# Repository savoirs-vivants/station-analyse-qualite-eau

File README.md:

# Station d'Analyse de la Qualité de l'Eau 💧

Station autonome pour la surveillance de la qualité de l'eau. Ce dépôt contient l'intégralité de la conception matérielle (schémas et routage PCB) ainsi que le firmware d'acquisition.

## 🎯 Objectif du projet

Ce système a pour but de collecter, traiter, transmettre et enregistrer des données environnementales issues de différentes sondes. Il est conçu pour être autonome en énergie et low-cost.

**Paramètres mesurés :**
*  Température de l'eau
*  Température et Humidité de l'air
*  Conductivité / TDS
*  Turbidité
*  Débit/Hauteur d'eau

## 📁 Architecture du projet

Ce dépôt est organisé en deux parties distinctes :

* 🛠️ **`/hardware`** : Fichiers de conception de la carte électronique réalisés sous KiCad (Schémas, PCB, nomenclatures).
* 💻 **`/firmware`** : Code source en C gérant l'acquisition , le traitement des signaux capteurs et la logique système.

*Pour plus de détails techniques, veuillez consulter les fichiers `README.md` présents dans chacun de ces répertoires.*

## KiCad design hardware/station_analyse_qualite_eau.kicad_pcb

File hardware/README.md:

# 🛠️ Conception Matérielle (Hardware)

Ce dossier contient l'intégralité du projet de conception de la carte mère de la **Station d'Analyse de la Qualité de l'Eau**. La carte est architecturée autour d'un microcontrôleur ultra-basse consommation **STM32U083RC**.

## 📌 Caractéristiques Techniques

* **Microcontrôleur :** STM32U083RC (ARM Cortex-M0+, optimisation Low-Power).
* **Mémoire non volatile :** FeRAM (Ferroelectric RAM) via bus SPI pour le datalogging.
* **Connectivité Radio :**
    * **LoRaWAN :** Module radio intégré pour la transmission vers réseau ChirpStack.
    * **Bluetooth Low Energy (BLE) :** Pour la récupération locale des données en cas de problème avec le LoRa.

## 📂 Architecture du dossier KiCad

* `*.kicad_sch` : Schémas électriques hiérarchiques.
* `*.kicad_pcb` : Routage de la carte.
* `/production` : Fichiers de fabrication générés pour JLCPCB.
* `/3D_Models` : Fichiers STEP pour le rendu 3D.

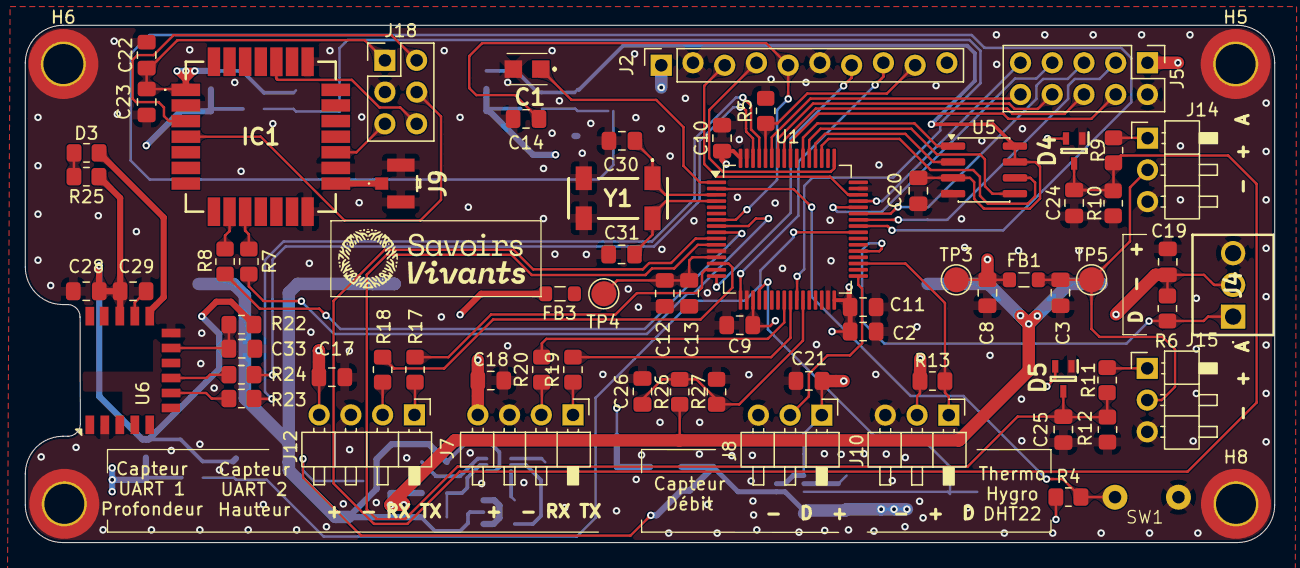
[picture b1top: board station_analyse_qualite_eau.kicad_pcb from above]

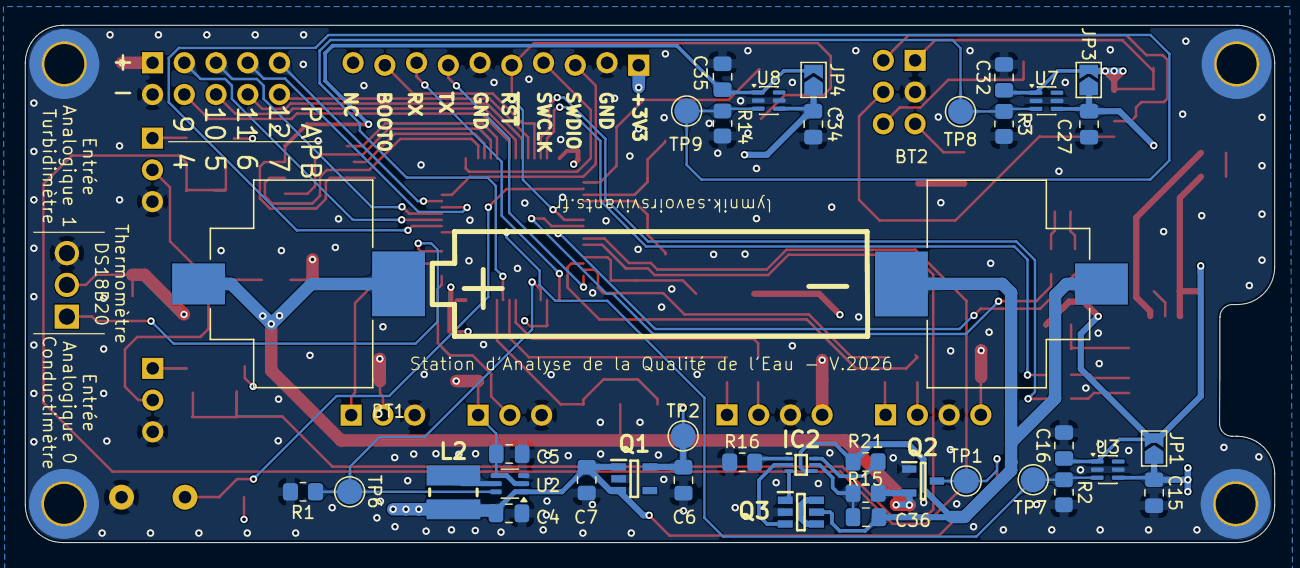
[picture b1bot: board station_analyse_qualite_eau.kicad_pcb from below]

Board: 4 copper layers, 100.0 x 41.4 mm, 112 parts (38 on the bottom side), 76 nets.

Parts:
BT1, BT2: 254; BAT_254
C1: CPH3225A
C2, C3, C4, C8, C22, C28: 10u; C_0805_2012Metric_Pad1.18x1.45mm_HandSolder
C5, C6: 2.2u; C_0805_2012Metric_Pad1.18x1.45mm_HandSolder
C7, C12, C15, C17, C18, C19, C21, C24, C25, C27, C34: 1u; C_0805_2012Metric_Pad1.18x1.45mm_HandSolder
C9, C10, C11, C13, C14, C16, C20, C23, C26, C29, C32, C33, C35, C36: 100n; C_0805_2012Metric_Pad1.18x1.45mm_HandSolder
C30, C31: 6.8p; C_0805_2012Metric_Pad1.18x1.45mm_HandSolder
D3: LED; R_0805_2012Metric_Pad1.20x1.40mm_HandSolder
D4, D5: BAV199W; SOT65P210X110-3N
FB1, FB3: BLM21AG601SH1D; L_0805_2012Metric_Pad1.05x1.20mm_HandSolder
H5, H6, H7, H8: MountingHole_Pad; MountingHole_3.2mm_M3_DIN965_Pad_TopBottom
IC1: 317990687
IC2: S-82B1AAB-I6T1U; SOTFL50P180X50-6N
J2: SWD+DEBUG UART; StaggeredHeader_1x10_P2.54mm_Vertical
J4: Terminal_DS18B20; TBC05031GG
J5: Conn_02x05_Odd_Even; PinHeader_2x05_P2.54mm_Vertical
J7: Conn_Capteur_UART_2; Custom_PinHeader_1x04_P2.54mm_Horizontal
J8: Terminal_Water_Flow_Sensor; Custom_PinHeader_1x03_P2.54mm_Horizontal
J9: U.FL; UFLRSMT10
J10: Conn_DHT22; Custom_PinHeader_1x03_P2.54mm_Horizontal
J12: Conn_Capteur_UART_1; Custom_PinHeader_1x04_P2.54mm_Horizontal
J14, J15: Conn_AN; Custom_PinHeader_1x03_P2.54mm_Horizontal
J18: Conn_02x03_Odd_Even; PinHeader_2x03_P2.54mm_Vertical
JP1: Bypass LS BLE; SolderJumper-2_P1.3mm_Open_TrianglePad1.0x1.5mm
JP3: Bypass LS LoRa; SolderJumper-2_P1.3mm_Open_TrianglePad1.0x1.5mm
JP4: Bypass LS FRAM; SolderJumper-2_P1.3mm_Open_TrianglePad1.0x1.5mm
L2: 4,7u; 744031004
Q1: TPS7A0233PDBVR; SOT95P280X145-5N
Q2: DMG2305UX-7; SOT96P240X115-3N
Q3: FDC6561AN; SOT95P280X110-6N
R1, R2, R3, R14: 100k; R_0805_2012Metric_Pad1.20x1.40mm_HandSolder
R4, R5, R9, R10, R11, R12, R22: 10k; R_0805_2012Metric_Pad1.20x1.40mm_HandSolder
R6, R13: 4.7k; R_0805_2012Metric_Pad1.20x1.40mm_HandSolder
R7, R8, R17, R18, R19, R20, R23, R24: 22R; R_0805_2012Metric_Pad1.20x1.40mm_HandSolder
R15: 330; R_0805_2012Metric_Pad1.20x1.40mm_HandSolder
R16, R21: 1k; R_0805_2012Metric_Pad1.20x1.40mm_HandSolder
R25: 330R; R_0805_2012Metric_Pad1.20x1.40mm_HandSolder
R26, R27: 1M; R_0805_2012Metric_Pad1.20x1.40mm_HandSolder
SW1: SW_Push; P5.08mm
TP1: TP_BATT; TestPoint_Pad_D2.0mm
TP2: TP_3V3; TestPoint_Pad_D2.0mm
TP3: TP_5V; TestPoint_Pad_D2.0mm
TP4: TP_3.3VA; TestPoint_Pad_D2.0mm
TP5: TP_5VA; TestPoint_Pad_D2.0mm
TP6: TP_EN_BOOST; TestPoint_Pad_D2.0mm
TP7: TP_EN_LS_BLE; TestPoint_Pad_D2.0mm
TP8: TP_EN_LS_LORA; TestPoint_Pad_D2.0mm
TP9: TP_EN_LS_FRAM; TestPoint_Pad_D2.0mm
U1: STM32U083RCTx; LQFP-64_10x10mm_P0.5mm
U2: TPS61222DCK; Texas_R-PDSO-G6
U3, U7, U8: SiP32431DR3; SOT-363_SC-70-6
U5: MB85RS2MTAPNF; SOIC-8_3.9x4.9mm_P1.27mm
U6: RN4871; Microchip_RN4871
Y1: G43270018

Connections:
1-Wire: J4.1, R6.2, U1.37 (PC6)
+3.3VA: C12.1, C13.1, FB3.2, TP4.1 (1_1), U1.13 (VDDA)
+3V3: C2.1, C6.2, C9.1, C10.1, C11.1, C15.1, C27.1, C34.1, D4.2 (K), D5.2 (K), FB3.1, J2.1, J5.1, JP1.1 (A), JP3.1 (A), JP4.1 (A), Q1.5 (OUT), R4.1, TP2.1 (1_1), U1.19 (VDD), U1.32 (VDD), U1.64 (VDD), U3.4 (IN), U7.4 (IN), U8.4 (IN)
+3V3_BLE: C16.1, C28.1, C29.1, D3.2 (A), JP1.2 (B), R22.2, U3.1 (OUT), U6.14 (VBAT)
+3V3_FRAM: C20.1, C35.1, JP4.2 (B), U5.3 (~WP), U5.7 (~HOLD), U5.8 (VDD), U8.1 (OUT)
+3V3_LoRa: C22.1, C23.1, C32.1, IC1.1 (VCC), J18.1, JP3.2 (B), U7.1 (OUT)
+5V: C5.2, C8.2, C17.1, C18.1, C19.1, C21.1, FB1.1, J4.2, J7.4, J8.1, J10.2, J12.4, R6.1, R13.1, TP3.1 (1_1), U2.2 (FB), U2.4 (VOUT)
+5VA: C3.2, FB1.2, J14.2, J15.2, TP5.1 (1_1)
+BATT: BT1.P1, BT1.P2, Q2.2 (S), R15.2, R26.1
-BATT: BT2.P1, BT2.P2, C36.2, IC2.4 (VSS), Q3.5 (S1), R21.1
/Radio Frequency/BOOT_LoRa: IC1.24 (PB13), J18.6
/Radio Frequency/RST_LoRa: IC1.17 (RST), J18.5
/Radio Frequency/SWCLK_LoRa: IC1.4 (PA14), J18.4
/Radio Frequency/SWDIO_LoRa: IC1.3 (PA13), J18.2
AI0: C25.1, D5.3 (C), R11.2, R12.1, U1.11 (PC3)
AI1: C24.1, D4.3 (C), R9.2, R10.1, U1.10 (PC2)
AN_Battery: C26.1, R26.2, R27.1, U1.27 (PB1)
BOOT0: J2.9, R5.1, U1.60 (PF3)
DHT22: J10.1, R13.2, U1.35 (PB14)
EN_BOOST: R1.1, TP6.1 (1_1), U1.20 (PA4), U2.6 (EN)
EN_LS_BLE: R2.1, TP7.1 (1_1), U1.40 (PC9), U3.3 (ON)
EN_LS_FRAM: R14.1, TP9.1 (1_1), U1.41 (PA8), U8.3 (ON)
EN_LS_LoRa: R3.1, TP8.1 (1_1), U1.26 (PB0), U7.3 (ON)
GND: C1.2 (-), C2.2, C3.1, C4.1, C5.1, C6.1, C7.1, C8.1, C9.2, C10.2, C11.2, C12.2, C13.2, C14.2, C15.2, C16.2, C17.2, C18.2, C19.2, C20.2, C21.2, C22.2, C23.2, C24.2, C25.2, C26.2, C27.2, C28.2, C29.2, C30.2, C31.2, C32.2, C33.2, C34.2, C35.2, D4.1 (A), D5.1 (A), H5.1 (1_1), H6.1 (1_1), H7.1 (1_1), H8.1 (1_1), IC1.2 (GND_1), IC1.14 (GND_2), IC1.16 (GND_3), IC1.22 (GND_4), J2.2, J2.6, J4.3, J5.2, J7.3, J8.3, J9.2 (Ext), J9.3 (Ext), J10.3, J12.3, J14.3, J15.3, J18.3, Q1.2 (GND), Q2.1 (G), Q3.2 (S2), R1.2, R2.2, R3.2, R5.2, R10.2, R12.2, R14.2, R16.1, R27.2, SW1.2, U1.12 (VSSA), U1.18 (VSS), U1.31 (VSS), U1.47 (VSS), U1.63 (VSS), U2.3 (GND), U3.2 (GND), U3.5 (GND), U5.4 (GND), U6.2 (GND), U6.11 (P0_0), U6.13 (GND), U7.2 (GND), U7.5 (GND), U8.2 (GND), U8.5 (GND), Y1.2 (GND_1), Y1.3 (GND_2)
IMP: J8.2, U1.33 (PB12)
MISO: U1.52 (PC11), U5.2 (SO)
MOSI: U1.53 (PC12), U5.5 (SI)
unnamed: D3.1 (K), R25.2
unnamed: IC1.10 (PB6), R7.1
unnamed: IC1.9 (PB7), R8.1
unnamed: IC1.15 (RFIO), J9.1 (In)
unnamed: IC2.2 (CO), Q3.3 (G2)
unnamed: IC2.6 (CTL), R21.2
unnamed: IC2.3 (DO), Q3.1 (G1)
unnamed: C36.1, IC2.5 (VDD), R15.1
unnamed: IC2.1 (VM), R16.2
unnamed: J7.1, R19.1
unnamed: J7.2, R20.1
unnamed: J12.1, R17.1
unnamed: J12.2, R18.1
unnamed: J14.1, R9.1
unnamed: J15.1, R11.1
unnamed: Q3.4 (D2), Q3.6 (D1)
unnamed: L2.2, U2.5 (L)
unnamed: R25.1, U6.12 (P0_2)
unnamed: C33.1, R22.1, U6.10 (RST)
unnamed: R23.2, U6.7 (UART_RX)
unnamed: R24.2, U6.8 (UART_TX)
OSC32_IN: C30.1, U1.3 (PC14), Y1.1 (CRYSTAL_1)
OSC32_OUT: C31.1, U1.4 (PC15), Y1.4 (CRYSTAL_2)
PA9: J5.3, U1.42 (PA9)
PA10: J5.5, U1.43 (PA10)
PA11: J5.7, U1.44 (PA11)
PA12: J5.9, U1.45 (PA12)
PB4: J5.4, U1.56 (PB4)
PB5: J5.6, U1.57 (PB5)
PB6: J5.8, U1.58 (PB6)
PB7: J5.10, U1.59 (PB7)
RX_BLE: R23.1, U1.61 (PB8)
RX_C1: R18.2, U1.14 (PA0)
RX_C2: R20.2, U1.24 (PC4)
RX_LoRa: R8.2, U1.9 (PC1)
SCLK: U1.51 (PC10), U5.6 (SCK)
SWCLK: J2.4, U1.49 (PA14)
SWDIO: J2.3, U1.46 (PA13)
TX_BLE: R24.1, U1.62 (PB9)
TX_C1: R17.2, U1.15 (PA1)
TX_C2: R19.2, U1.25 (PC5)
TX_LoRa: R7.2, U1.8 (PC0)
UART_DEBUG_RX: J2.8, U1.17 (PA3)
UART_DEBUG_TX: J2.7, U1.16 (PA2)
VCC: C4.2, C7.2, L2.1, Q1.1 (IN), Q1.3 (EN), Q2.3 (D), TP1.1 (1_1), U2.1 (VIN)
V_BACKUP: C1.1 (+), U1.1 (VBAT)
~CS0: U1.54 (PD2), U5.1 (~CS)
~RST: C14.1, J2.5, U1.7 (PF2)
~WAKE_UP: R4.2, SW1.1, U1.2 (PC13)

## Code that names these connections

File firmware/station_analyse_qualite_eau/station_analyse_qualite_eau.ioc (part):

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Mcu.Name=STM32U083RCTx
Mcu.Package=LQFP64
Mcu.UserName=STM32U083RCTx
PA0.Mode=Asynchronous
PA0.Signal=USART4_TX
PA1.Mode=Asynchronous
PA1.Signal=USART4_RX
PA13\ (SWDIO).GPIOParameters=GPIO_Label
PA13\ (SWDIO).GPIO_Label=SWDIO
PA13\ (SWDIO).Signal=DEBUG_JTMS-SWDIO
PA14\ (SWCLK).GPIOParameters=GPIO_Label
PA14\ (SWCLK).GPIO_Label=SWCLK
PA14\ (SWCLK).Signal=DEBUG_JTCK-SWCLK
PA2.Signal=USART2_TX
PA3.Signal=USART2_RX
PA4.GPIOParameters=GPIO_Label
PA4.GPIO_Label=EN_LS_C5V
PA4.Signal=GPIO_Output
PA8.GPIOParameters=GPIO_Label
PA8.GPIO_Label=EN_LS_FRAM
PA8.Signal=GPIO_Output
PB0.GPIOParameters=GPIO_Label
PB0.GPIO_Label=EN_LS_LoRa
PB0.Signal=GPIO_Output
PB1.Mode=IN18
PB1.Signal=ADC1_IN18
PB12.GPIOParameters=GPIO_Label
PB12.GPIO_Label=IMP
PB12.Signal=GPIO_Input
PB14.Signal=S_TIM15_CH1
PB8.Mode=Asynchronous
PB8.Signal=USART3_TX
PB9.Mode=Asynchronous
PB9.Signal=USART3_RX
PC0.Mode=Asynchronous
PC0.Signal=LPUART1_RX
PC1.Mode=Asynchronous
PC1.Signal=LPUART1_TX
PC10.Mode=Full_Duplex_Master
PC10.Signal=SPI3_SCK
PC11.Mode=Full_Duplex_Master
PC11.Signal=SPI3_MISO
PC12.Mode=Full_Duplex_Master
PC12.Signal=SPI3_MOSI
PC13.GPIOParameters=GPIO_PuPd,GPIO_Label,GPIO_ModeDefaultEXTI
PC13.GPIO_Label=EN_BLE
PC13.GPIO_ModeDefaultEXTI=GPIO_MODE_IT_FALLING
PC13.GPIO_PuPd=GPIO_PULLUP
PC13.Signal=GPXTI13
PC14-OSC32_IN.GPIOParameters=GPIO_Label
PC14-OSC32_IN.GPIO_Label=OSC32_IN
PC14-OSC32_IN.Mode=LSE-External-Oscillator
PC14-OSC32_IN.Signal=RCC_OSC32_IN
PC15-OSC32_OUT.GPIOParameters=GPIO_Label
PC15-OSC32_OUT.GPIO_Label=OSC32_OUT
PC15-OSC32_OUT.Mode=LSE-External-Oscillator
PC15-OSC32_OUT.Signal=RCC_OSC32_OUT
PC2.GPIOParameters=GPIO_Label
PC2.GPIO_Label=AI1
PC2.Signal=SharedAnalog_PC2
PC3.GPIOParameters=GPIO_Label
PC3.GPIO_Label=AI0
PC3.Signal=SharedAnalog_PC3
PC4.Mode=Asynchronous
PC4.Signal=LPUART3_TX
PC5.Mode=Asynchronous
PC5.Signal=LPUART3_RX
PC6.GPIOParameters=GPIO_PuPdOD
PC6.GPIO_PuPdOD=GPIO_NOPULL
PC6.Mode=Half_duplex(single_wire_mode)
PC6.Signal=LPUART2_TX
PC9.GPIOParameters=GPIO_Label
PC9.GPIO_Label=EN_LS_BLE
PC9.Signal=GPIO_Output
PD2.GPIOParameters=GPIO_Label
PD2.GPIO_Label=SPI3_CS0
PD2.Signal=GPIO_Output
PF0-OSC_IN.GPIOParameters=GPIO_Label
PF0-OSC_IN.GPIO_Label=OSC_IN
PF0-OSC_IN.Signal=RCC_OSC_IN
PF1-OSC_OUT.GPIOParameters=GPIO_Label
PF1-OSC_OUT.GPIO_Label=OSC_OUT
PF1-OSC_OUT.Signal=RCC_OSC_OUT
RCC.HSE_VALUE=4000000
RCC.SYSCLKFreq_VALUE=16000000
RCC.SYSCLKSource=RCC_SYSCLKSOURCE_MSI
board=NUCLEO-U083RC
boardIOC=true

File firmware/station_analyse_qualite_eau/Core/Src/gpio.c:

/* USER CODE BEGIN Header */
/**
  ******************************************************************************
  * @file    gpio.c
  * @brief   This file provides code for the configuration
  *          of all used GPIO pins.
  ******************************************************************************
  * @attention
  *
  * Copyright (c) 2026 STMicroelectronics.
  * All rights reserved.
  *
  * This software is licensed under terms that can be found in the LICENSE file
  * in the root directory of this software component.
  * If no LICENSE file comes with this software, it is provided AS-IS.
  *
  ******************************************************************************
  */
/* USER CODE END Header */

/* Includes ------------------------------------------------------------------*/
#include "gpio.h"

/* USER CODE BEGIN 0 */

/* USER CODE END 0 */

/*----------------------------------------------------------------------------*/
/* Configure GPIO                                                             */
/*----------------------------------------------------------------------------*/
/* USER CODE BEGIN 1 */

/* USER CODE END 1 */

/** Configure pins
     PC14-OSC32_IN   ------> RCC_OSC32_IN
     PC15-OSC32_OUT   ------> RCC_OSC32_OUT
     PF0-OSC_IN   ------> RCC_OSC_IN
     PF1-OSC_OUT   ------> RCC_OSC_OUT
     PA13 (SWDIO)   ------> DEBUG_JTMS-SWDIO
     PA14 (SWCLK)   ------> DEBUG_JTCK-SWCLK
*/
void MX_GPIO_Init(void)
{

  GPIO_InitTypeDef GPIO_InitStruct = {0};

  /* GPIO Ports Clock Enable */
  __HAL_RCC_GPIOC_CLK_ENABLE();
  __HAL_RCC_GPIOF_CLK_ENABLE();
  __HAL_RCC_GPIOA_CLK_ENABLE();
  __HAL_RCC_GPIOB_CLK_ENABLE();
  __HAL_RCC_GPIOD_CLK_ENABLE();

  /*Configure GPIO pin Output Level */
  HAL_GPIO_WritePin(GPIOA, EN_LS_C5V_Pin|EN_LS_FRAM_Pin, GPIO_PIN_RESET);

  /*Configure GPIO pin Output Level */
  HAL_GPIO_WritePin(EN_LS_LoRa_GPIO_Port, EN_LS_LoRa_Pin, GPIO_PIN_RESET);

  /*Configure GPIO pin Output Level */
  HAL_GPIO_WritePin(EN_LS_BLE_GPIO_Port, EN_LS_BLE_Pin, GPIO_PIN_RESET);

  /*Configure GPIO pin Output Level */
  HAL_GPIO_WritePin(SPI3_CS0_GPIO_Port, SPI3_CS0_Pin, GPIO_PIN_RESET);

  /*Configure GPIO pin : EN_BLE_Pin */
  GPIO_InitStruct.Pin = EN_BLE_Pin;
  GPIO_InitStruct.Mode = GPIO_MODE_IT_FALLING;
  GPIO_InitStruct.Pull = GPIO_PULLUP;
  HAL_GPIO_Init(EN_BLE_GPIO_Port, &GPIO_InitStruct);

  /*Configure GPIO pins : PF2 PF3 */
  GPIO_InitStruct.Pin = GPIO_PIN_2|GPIO_PIN_3;
  GPIO_InitStruct.Mode = GPIO_MODE_ANALOG;
  GPIO_InitStruct.Pull = GPIO_NOPULL;
  HAL_GPIO_Init(GPIOF, &GPIO_InitStruct);

  /*Configure GPIO pins : EN_LS_C5V_Pin EN_LS_FRAM_Pin */
  GPIO_InitStruct.Pin = EN_LS_C5V_Pin|EN_LS_FRAM_Pin;
  GPIO_InitStruct.Mode = GPIO_MODE_OUTPUT_PP;
  GPIO_InitStruct.Pull = GPIO_NOPULL;
  GPIO_InitStruct.Speed = GPIO_SPEED_FREQ_LOW;
  HAL_GPIO_Init(GPIOA, &GPIO_InitStruct);

  /*Configure GPIO pins : PA6 PA7 PA9 PA10
                           PA11 PA12 PA15 */
  GPIO_InitStruct.Pin = GPIO_PIN_6|GPIO_PIN_7|GPIO_PIN_9|GPIO_PIN_10
                          |GPIO_PIN_11|GPIO_PIN_12|GPIO_PIN_15;
  GPIO_InitStruct.Mode = GPIO_MODE_ANALOG;
  GPIO_InitStruct.Pull = GPIO_NOPULL;
  HAL_GPIO_Init(GPIOA, &GPIO_InitStruct);

  /*Configure GPIO pin : EN_LS_LoRa_Pin */
  GPIO_InitStruct.Pin = EN_LS_LoRa_Pin;
  GPIO_InitStruct.Mode = GPIO_MODE_OUTPUT_PP;
  GPIO_InitStruct.Pull = GPIO_NOPULL;
  GPIO_InitStruct.Speed = GPIO_SPEED_FREQ_LOW;
  HAL_GPIO_Init(EN_LS_LoRa_GPIO_Port, &GPIO_InitStruct);

  /*Configure GPIO pins : PB2 PB10 PB11 PB13
                           PB15 PB3 PB4 PB5
                           PB6 PB7 */
  GPIO_InitStruct.Pin = GPIO_PIN_2|GPIO_PIN_10|GPIO_PIN_11|GPIO_PIN_13
                          |GPIO_PIN_15|GPIO_PIN_3|GPIO_PIN_4|GPIO_PIN_5
                          |GPIO_PIN_6|GPIO_PIN_7;
  GPIO_InitStruct.Mode = GPIO_MODE_ANALOG;
  GPIO_InitStruct.Pull = GPIO_NOPULL;
  HAL_GPIO_Init(GPIOB, &GPIO_InitStruct);

  /*Configure GPIO pin : IMP_Pin */
  GPIO_InitStruct.Pin = IMP_Pin;
  GPIO_InitStruct.Mode = GPIO_MODE_INPUT;
  GPIO_InitStruct.Pull = GPIO_NOPULL;
  HAL_GPIO_Init(IMP_GPIO_Port, &GPIO_InitStruct);

  /*Configure GPIO pins : PC7 PC8 */
  GPIO_InitStruct.Pin = GPIO_PIN_7|GPIO_PIN_8;
  GPIO_InitStruct.Mode = GPIO_MODE_ANALOG;
  GPIO_InitStruct.Pull = GPIO_NOPULL;
  HAL_GPIO_Init(GPIOC, &GPIO_InitStruct);

  /*Configure GPIO pin : EN_LS_BLE_Pin */
  GPIO_InitStruct.Pin = EN_LS_BLE_Pin;
  GPIO_InitStruct.Mode = GPIO_MODE_OUTPUT_PP;
  GPIO_InitStruct.Pull = GPIO_NOPULL;
  GPIO_InitStruct.Speed = GPIO_SPEED_FREQ_LOW;
  HAL_GPIO_Init(EN_LS_BLE_GPIO_Port, &GPIO_InitStruct);

  /*Configure GPIO pin : SPI3_CS0_Pin */
  GPIO_InitStruct.Pin = SPI3_CS0_Pin;
  GPIO_InitStruct.Mode = GPIO_MODE_OUTPUT_PP;
  GPIO_InitStruct.Pull = GPIO_NOPULL;
  GPIO_InitStruct.Speed = GPIO_SPEED_FREQ_LOW;
  HAL_GPIO_Init(SPI3_CS0_GPIO_Port, &GPIO_InitStruct);

  /* EXTI interrupt init*/
  HAL_NVIC_SetPriority(EXTI4_15_IRQn, 0, 0);
  HAL_NVIC_EnableIRQ(EXTI4_15_IRQn);

}

/* USER CODE BEGIN 2 */

/* USER CODE END 2 */

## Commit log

2026-06-05 add readme
2026-06-08 ajout firmware
2026-06-09 added doxygen documentation
2026-06-09 Fix: Conversion du sous-module STM32 en dossier standard
